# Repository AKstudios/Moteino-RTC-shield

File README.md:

# Moteino RTC shield

This is an RTC Shield for Moteino based on Maxim DS3234. Recommended library to use: https://github.com/OSBSS/DS3234lib3

To force interrupts in backup battery/low power mode (~1uA), don’t solder the 10K resistor, enable Arduino internal pullups
on pin 4 instead and pin-power the RTC when needed by turning pin 3 on. Backup battery should last 1-2 years @ 30 second alarm intervals depending on temperature variations.

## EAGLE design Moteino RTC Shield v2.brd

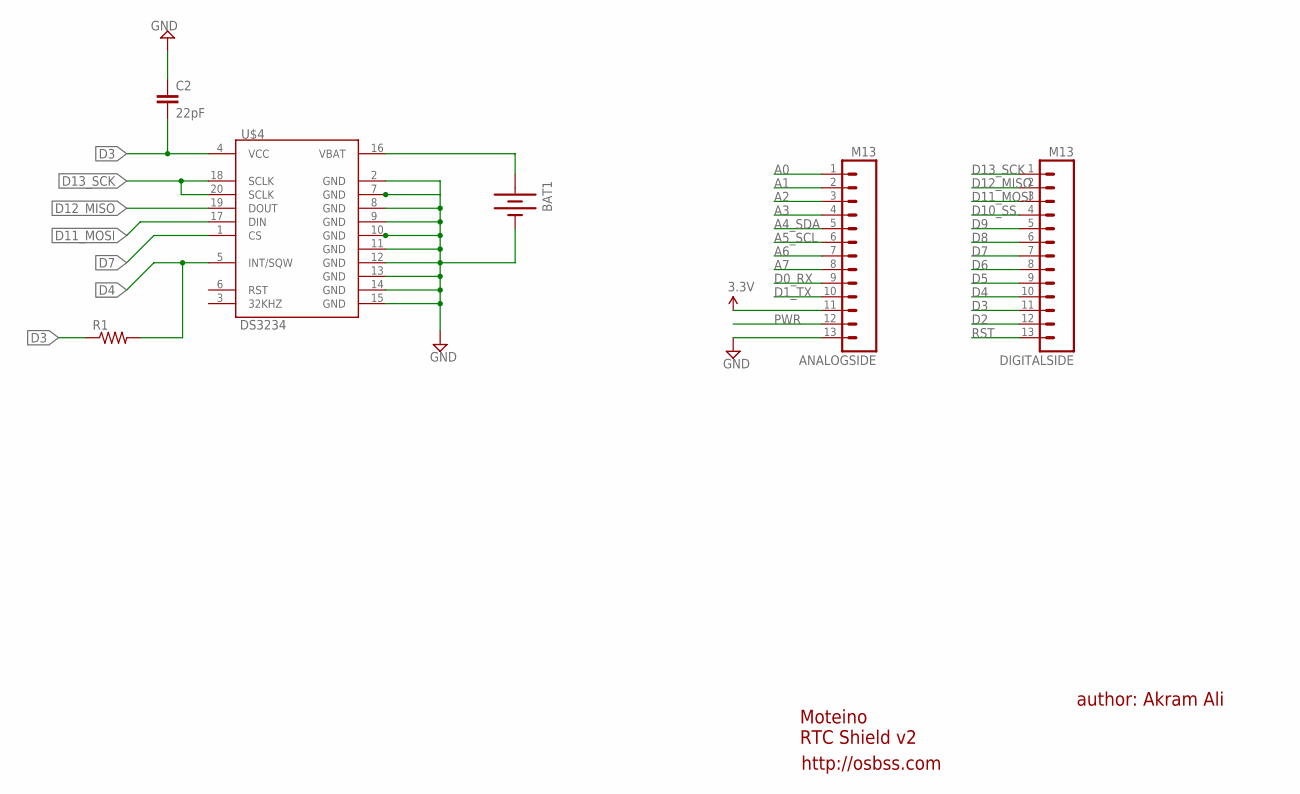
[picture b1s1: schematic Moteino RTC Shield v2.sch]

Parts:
ANALOGSIDE: M13; 1X13
BAT1: BATTERY12MM; BATTCON_12MM
C2: 22pF; 0805
DIGITALSIDE: M13; 1X13
R1: RESISTOR0805-RES; 0805
U$4: DS3234

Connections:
A0: ANALOGSIDE.1
A1: ANALOGSIDE.2
A2: ANALOGSIDE.3
A3: ANALOGSIDE.4
A4_SDA: ANALOGSIDE.5
A5_SCL: ANALOGSIDE.6
A6: ANALOGSIDE.7
A7: ANALOGSIDE.8
D0_RX: ANALOGSIDE.9
D1_TX: ANALOGSIDE.10
D2: DIGITALSIDE.12
D3: C2.2, DIGITALSIDE.11, R1.1, U$4.4 (VCC)
D4: DIGITALSIDE.10, R1.2, U$4.5 (INT/SQW)
D5: DIGITALSIDE.9
D6: DIGITALSIDE.8
D7: DIGITALSIDE.7, U$4.1 (CS)
D8: DIGITALSIDE.6
D9: DIGITALSIDE.5
D10_SS: DIGITALSIDE.4
D11_MOSI: DIGITALSIDE.3, U$4.17 (DIN)
D12_MISO: DIGITALSIDE.2, U$4.19 (DOUT)
D13_SCK: DIGITALSIDE.1, U$4.18 (SCLK), U$4.20 (SCLK)
GND: ANALOGSIDE.13, BAT1.GND (-), C2.1, U$4.2 (GND), U$4.7 (GND), U$4.8 (GND), U$4.9 (GND), U$4.10 (GND), U$4.11 (GND), U$4.12 (GND), U$4.13 (GND), U$4.14 (GND), U$4.15 (GND)
unnamed: BAT1.PWR@1 (+), U$4.16 (VBAT)
PWR: ANALOGSIDE.12
RST: DIGITALSIDE.13
VCC: ANALOGSIDE.11

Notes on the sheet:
Moteino RTC Shield v2
author: Akram Ali
http://osbss.com

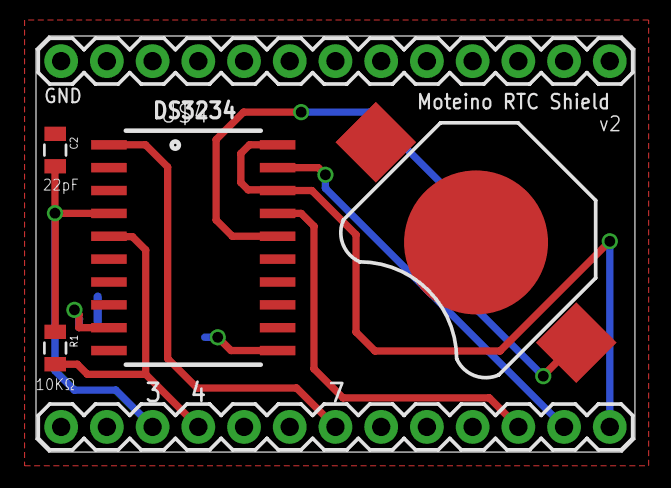
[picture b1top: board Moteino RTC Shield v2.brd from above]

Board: 2 copper layers, 33.3 x 23.1 mm, 7 parts (1 on the bottom side), 8 nets.

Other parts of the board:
U$3: OSHW-LOGO-S

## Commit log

2016-07-02 Moteino RTC Shield
    DS3234 RTC. To force interrupts in backup battery/low power mode
    (~1uA), don’t solder the 10K resistor, enable Arduino internal pullups
    on pin 4 instead and pin-power the RTC when needed by turning pin 3 on.
    Backup battery should last ~1 year @ 30 second alarm intervals
2016-07-02 Added PNGs
2016-07-02 Images

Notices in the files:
parts and their libraries:
SparkFun-Connectors: Licensing: CC v3.0 Share-Alike You are welcome to use this library for commercial purposes.
SparkFun-FreqCtrl: Licensing: Creative Commons ShareAlike 4.0 International - https://creativecommons.org/licenses/by-sa/4.0
